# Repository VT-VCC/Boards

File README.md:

# Board Layouts

This repository contains all of the layouts for the custom boards on the CERES cubesat.

- **Motherboard (Rev. C)** - The current main processor board.
- **Communications Board (Rev. A)** - The current combined PINAV GPS and Lithium Radio commications board.
- **GPS Board** and **Radio Board** - These are legacy designs.

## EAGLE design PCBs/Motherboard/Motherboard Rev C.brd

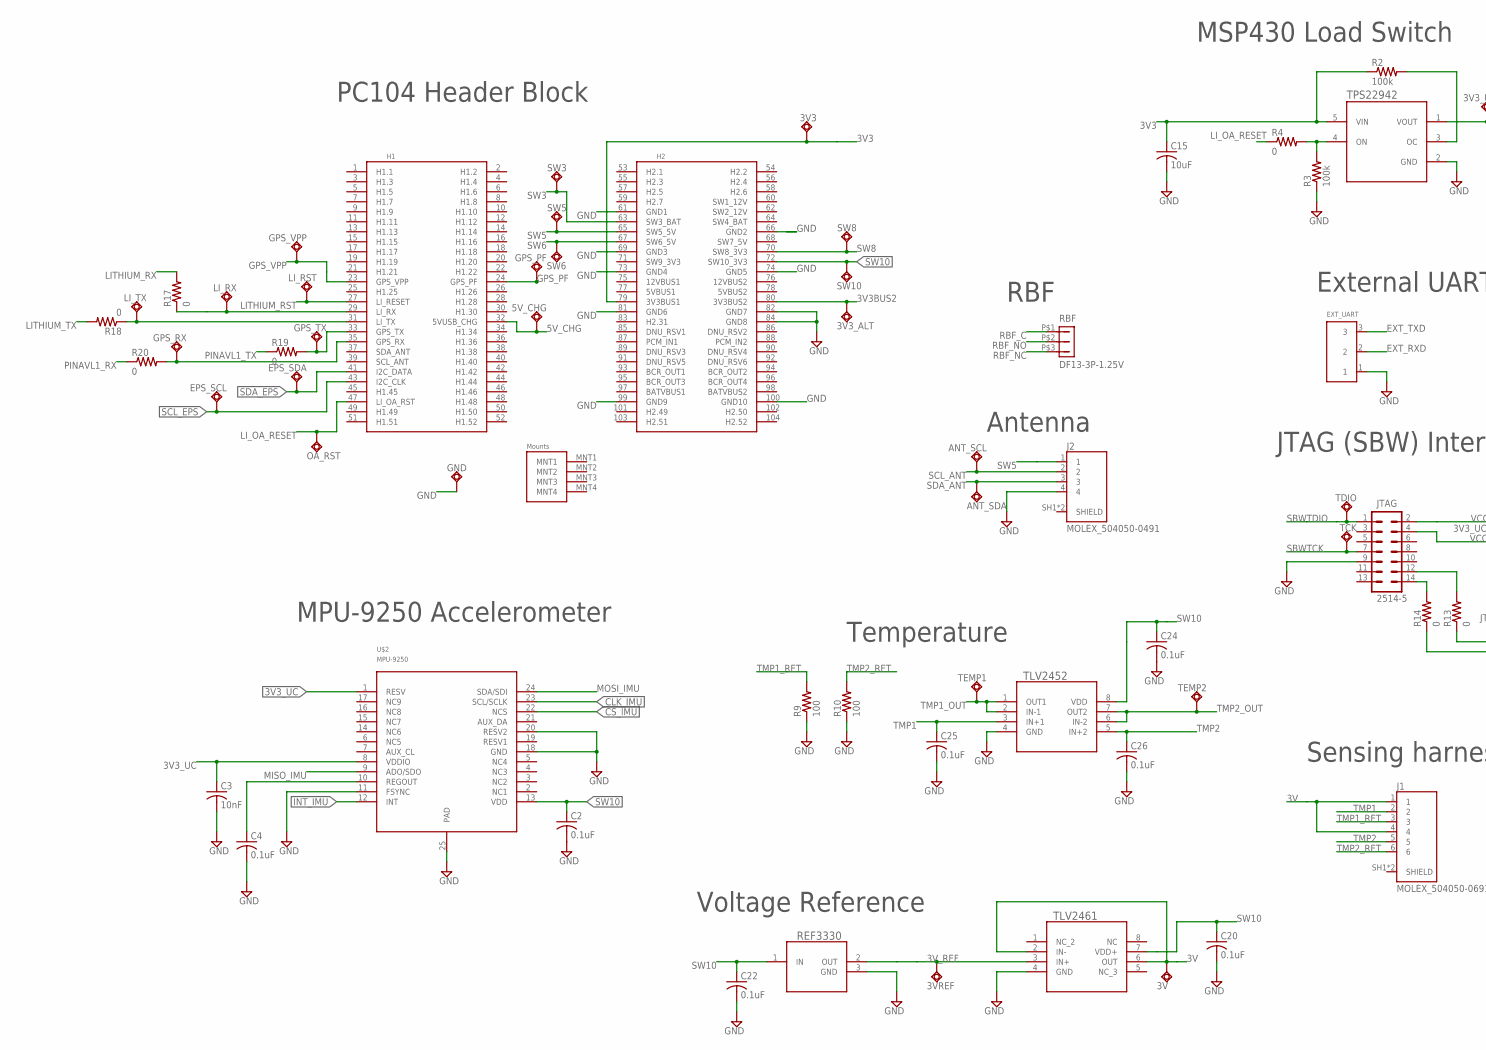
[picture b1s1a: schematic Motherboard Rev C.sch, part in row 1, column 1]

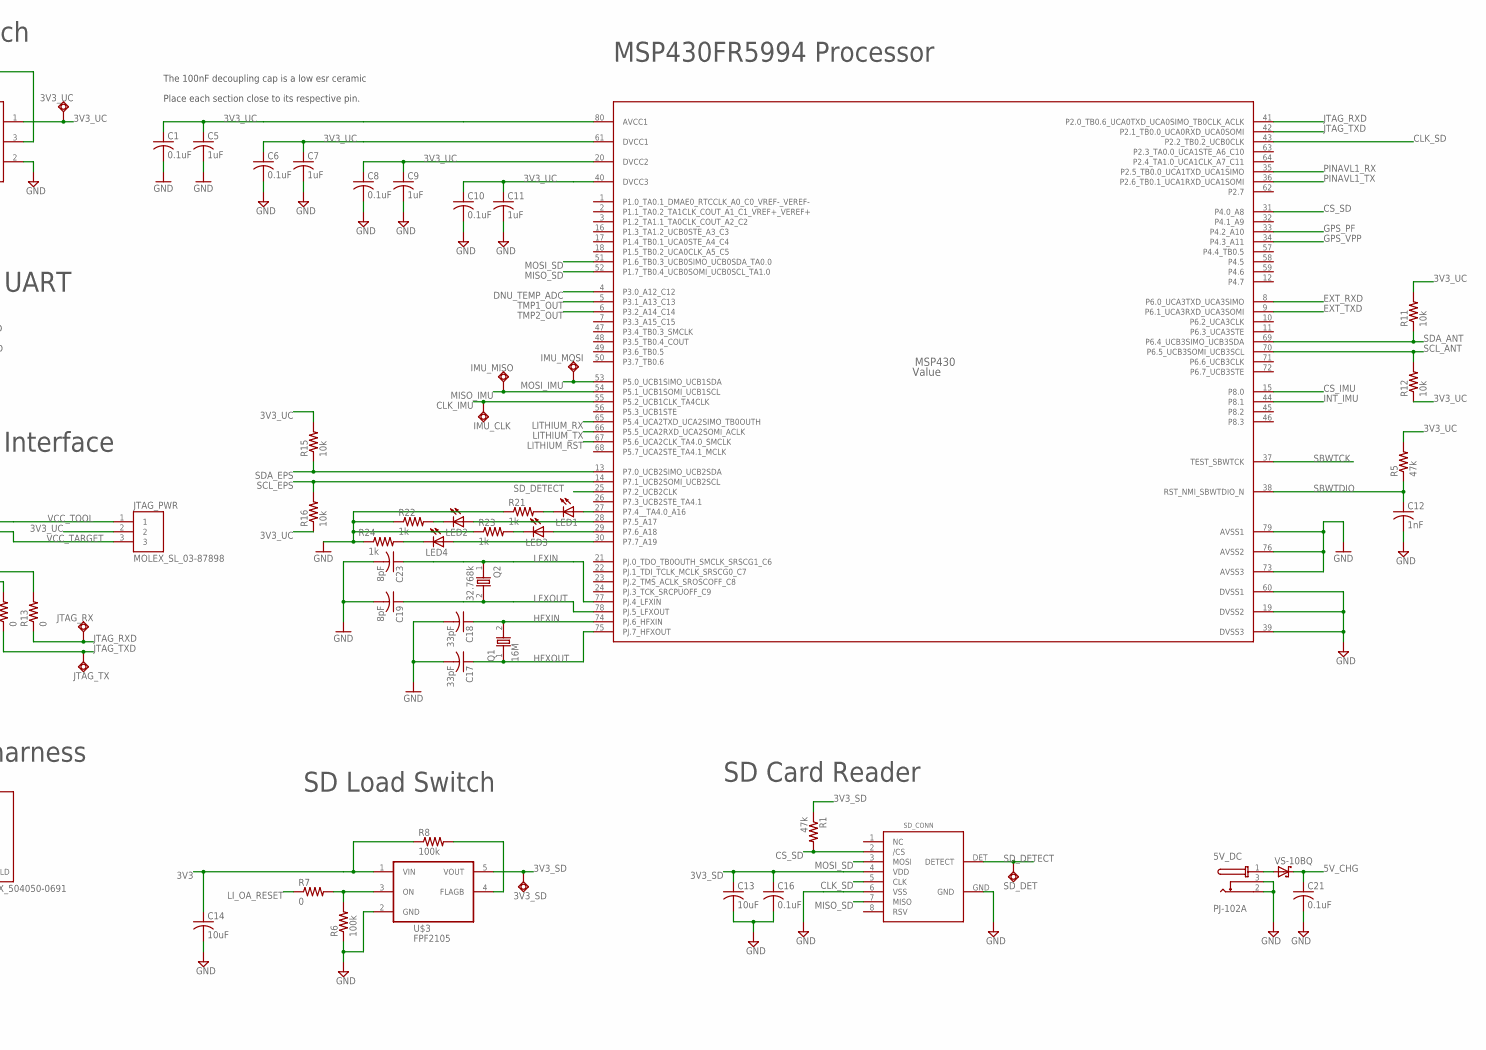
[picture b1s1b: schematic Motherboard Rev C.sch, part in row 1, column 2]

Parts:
3V, 3V3, 3V3_ALT, 3V3_SD, 3V3_UC, 3VREF, 5V_CHG: TPSQTP10SQ; TP10SQ
5V_DC: PJ-102A; CUI_PJ-102A
ANT_SCL: TPSQTP10SQ; TP10SQ
ANT_SDA: TPSQTP10SQ; TP10SQ
C1, C2, C4, C6, C8, C10, C16, C20, C21, C22, C24, C25, C26: 0.1uF; C0805
C3: 10nF; C0805
C5, C7, C9, C11: 1uF; C0805
C12: 1nF; C0805
C13, C14, C15: 10uF; C0805
C17, C18: 33pF; C0805
C19, C23: 8pF; C0805
EPS_SCL: TPSQTP10SQ; TP10SQ
EPS_SDA: TPSQTP10SQ; TP10SQ
EXT_UART: 90121-0763
GND: TPSQTP10SQ; TP10SQ
GPS_PF: TPSQTP10SQ; TP10SQ
GPS_RX: TPSQTP10SQ; TP10SQ
GPS_TX: TPSQTP10SQ; TP10SQ
GPS_VPP: TPSQTP10SQ; TP10SQ
IMU_CLK: TPSQTP06SQ; TP06SQ
IMU_MISO: TPSQTP06SQ; TP06SQ
IMU_MOSI: TPSQTP06SQ; TP06SQ
J1: MOLEX_504050-0691; MOLEX_5040500691
J2: MOLEX_504050-0491; MOLEX_5040500491
JTAG: 2514-5; PAK100/2500-5-14
JTAG_PWR: MOLEX_SL_03-87898; SL_87898_3
JTAG_RX: TPSQTP10SQ; TP10SQ
JTAG_TX: TPSQTP10SQ; TP10SQ
LED1, LED2, LED3, LED4: LEDSML0805; SML0805
LI_RST: TPSQTP10SQ; TP10SQ
LI_RX: TPSQTP10SQ; TP10SQ
LI_TX: TPSQTP10SQ; TP10SQ
MSP430: Value; PN0080A_N
OA_RST: TPSQTP10SQ; TP10SQ
Q1: 16M; 5X3.2
Q2: 32.768k; MS1V-T1K
R1, R5: 47k; R0805
R2, R3, R6, R8: 100k; R0805
R4, R7, R13, R14, R17, R18, R19, R20: 0; R0805
R9, R10: 100; R0805
R11, R12, R15, R16: 10k; R0805
R21, R22, R23, R24: 1k; R0805
RBF: DF13-3P-1.25V; DF13C-3P-1.25V
REF3330: REF3330_DBZ_3; DBZ3
SD_CONN: 502702-0891; 502702
SD_DET: TPSQTP10SQ; TP10SQ
SW3, SW5, SW6, SW8, SW10: TPSQTP10SQ; TP10SQ
TCK: TPSQTP10SQ; TP10SQ
TDIO: TPSQTP10SQ; TP10SQ
TEMP1, TEMP2: TPSQTP10SQ; TP10SQ
TLV2452: TLV2452; D8
TLV2461: TLV2461A_D_8; D8
TPS22942: TPS22942DCKR; DCK0005A
U$1: PC104_NO_DIMENSION
U$2: MPU-9250; LEAD-QFN24
U$3: FPF2105; SOT23-5
VS-10BQ: 10BQ015HM3; SMB

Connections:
3V: 3V.TP, J1.1, J1.4, TLV2461.2 (IN-), TLV2461.6 (OUT)
3V3: 3V3.TP, C14.1, C15.1, R2.1, R8.1, TPS22942.5 (VIN), U$1.79 (3V3BUS1), U$3.1 (VIN)
3V3BUS2: 3V3_ALT.TP, U$1.80 (3V3BUS2)
3V3_SD: 3V3_SD.TP, C13.1, C16.1, R1.1, SD_CONN.4 (VDD), U$3.5 (VOUT)
3V3_UC: 3V3_UC.TP, C1.1, C3.1, C5.1, C6.1, C7.1, C8.1, C9.1, C10.1, C11.1, JTAG_PWR.2, MSP430.20 (DVCC2), MSP430.40 (DVCC3), MSP430.61 (DVCC1), MSP430.80 (AVCC1), R5.2, R11.2, R12.1, R15.2, R16.1, TPS22942.1 (VOUT), U$2.1 (RESV), U$2.8 (VDDIO)
3V_REF: 3VREF.TP, REF3330.2 (OUT), TLV2461.3 (IN+)
5V_CHG: 5V_CHG.TP, C21.1, U$1.32 (5VUSB_CHG), VS-10BQ.C
CLK_IMU: IMU_CLK.TP, MSP430.55 (P5.2_UCB1CLK_TA4CLK), U$2.23 (SCL/SCLK)
CLK_SD: MSP430.43 (P2.2_TB0.2_UCB0CLK), SD_CONN.5 (CLK)
CS_IMU: MSP430.15 (P8.0), U$2.22 (NCS)
CS_SD: MSP430.31 (P4.0_A8), R1.2, SD_CONN.2 (/CS)
DNU_TEMP_ADC: MSP430.4 (P3.0_A12_C12)
EXT_RXD: EXT_UART.2, MSP430.8 (P6.0_UCA3TXD_UCA3SIMO)
EXT_TXD: EXT_UART.3, MSP430.9 (P6.1_UCA3RXD_UCA3SOMI)
GND: 5V_DC.2, 5V_DC.3, C1.2, C2.2, C3.2, C4.2, C5.2, C6.2, C7.2, C8.2, C9.2, C10.2, C11.2, C12.2, C13.2, C14.2, C15.2, C16.2, C17.2, C18.2, C19.2, C20.2, C21.2, C22.2, C23.2, C24.2, C25.2, C26.2, EXT_UART.1, GND.TP, J2.4, JTAG.9, MSP430.19 (DVSS2), MSP430.39 (DVSS3), MSP430.60 (DVSS1), MSP430.73 (AVSS3), MSP430.76 (AVSS2), MSP430.79 (AVSS1), R3.1, R6.1, R9.1, R10.1, R21.1, R22.1, R23.1, R24.1, REF3330.3 (GND), SD_CONN.6 (VSS), SD_CONN.GND, TLV2452.4 (GND), TLV2461.4 (GND), TPS22942.2 (GND), U$1.61 (GND1), U$1.66 (GND2), U$1.69 (GND3), U$1.73 (GND4), U$1.74 (GND5), U$1.81 (GND6), U$1.82 (GND7), U$1.84 (GND8), U$1.99 (GND9), U$1.100 (GND10), U$2.11 (FSYNC), U$2.18 (GND), U$2.20 (RESV2), U$2.25 (PAD), U$3.2 (GND)
GPS_PF: GPS_PF.TP, MSP430.33 (P4.2_A10), U$1.24 (GPS_PF)
GPS_VPP: GPS_VPP.TP, MSP430.34 (P4.3_A11), U$1.23 (GPS_VPP)
HFXIN: C18.1, MSP430.74 (PJ.6_HFXIN), Q1.2
HFXOUT: C17.1, MSP430.75 (PJ.7_HFXOUT), Q1.1
INT_IMU: MSP430.44 (P8.1), U$2.12 (INT)
JTAG_RXD: JTAG_RX.TP, MSP430.41 (P2.0_TB0.6_UCA0TXD_UCA0SIMO_TB0CLK_ACLK), R13.1
JTAG_TXD: JTAG_TX.TP, MSP430.42 (P2.1_TB0.0_UCA0RXD_UCA0SOMI), R14.1
LFXIN: C23.1, MSP430.77 (PJ.4_LFXIN), Q2.1
LFXOUT: C19.1, MSP430.78 (PJ.5_LFXOUT), Q2.2
LITHIUM_RST: LI_RST.TP, MSP430.67 (P5.6_UCA2CLK_TA4.0_SMCLK), U$1.27 (LI_RESET)
LITHIUM_RX: MSP430.65 (P5.4_UCA2TXD_UCA2SIMO_TB0OUTH), R17.2
LITHIUM_TX: MSP430.66 (P5.5_UCA2RXD_UCA2SOMI_ACLK), R18.2
LI_OA_RESET: OA_RST.TP, R4.1, R7.1, U$1.47 (LI_OA_RST)
MISO_IMU: IMU_MISO.TP, MSP430.54 (P5.1_UCB1SOMI_UCB1SCL), U$2.9 (ADO/SDO)
MISO_SD: MSP430.52 (P1.7_TB0.4_UCB0SOMI_UCB0SCL_TA1.0), SD_CONN.7 (MISO)
MOSI_IMU: IMU_MOSI.TP, MSP430.53 (P5.0_UCB1SIMO_UCB1SDA), U$2.24 (SDA/SDI)
MOSI_SD: MSP430.51 (P1.6_TB0.3_UCB0SIMO_UCB0SDA_TA0.0), SD_CONN.3 (MOSI)
unnamed: R2.2, TPS22942.3 (OC)
unnamed: R6.2, R7.2, U$3.3 (ON)
unnamed: C4.1, U$2.10 (REGOUT)
unnamed: LED1.C, R21.2
unnamed: R3.2, R4.2, TPS22942.4 (ON)
unnamed: LED1.A, MSP430.27 (P7.4__TA4.0_A16)
unnamed: R8.2, U$3.4 (FLAGB)
unnamed: JTAG.14, R14.2
unnamed: LED2.A, MSP430.28 (P7.5_A17)
unnamed: LED2.C, R22.2
unnamed: JTAG.12, R13.2
unnamed: LED3.A, MSP430.29 (P7.6_A18)
unnamed: 5V_DC.1, VS-10BQ.A
unnamed: LED3.C, R23.2
unnamed: LED4.A, MSP430.30 (P7.7_A19)
unnamed: LED4.C, R24.2
unnamed: GPS_RX.TP, R20.2, U$1.35 (GPS_RX)
unnamed: GPS_TX.TP, R19.2, U$1.33 (GPS_TX)
unnamed: LI_TX.TP, R18.1, U$1.31 (LI_TX)
unnamed: LI_RX.TP, R17.1, U$1.29 (LI_RX)
PINAVL1_RX: MSP430.35 (P2.5_TB0.0_UCA1TXD_UCA1SIMO), R20.1
PINAVL1_TX: MSP430.36 (P2.6_TB0.1_UCA1RXD_UCA1SOMI), R19.1
RBF_C: RBF.P$1 (1)
RBF_NC: RBF.P$3 (3)
RBF_NO: RBF.P$2 (2)
SBWTCK: JTAG.7, MSP430.37 (TEST_SBWTCK), TCK.TP
SBWTDIO: C12.1, JTAG.1, MSP430.38 (RST_NMI_SBWTDIO_N), R5.1, TDIO.TP
SCL_ANT: ANT_SCL.TP, J2.2, MSP430.70 (P6.5_UCB3SOMI_UCB3SCL), R12.2
SCL_EPS: EPS_SCL.TP, MSP430.14 (P7.1_UCB2SOMI_UCB2SCL), R16.2, U$1.43 (I2C_CLK)
SDA_ANT: ANT_SDA.TP, J2.3, MSP430.69 (P6.4_UCB3SIMO_UCB3SDA), R11.1
SDA_EPS: EPS_SDA.TP, MSP430.13 (P7.0_UCB2SIMO_UCB2SDA), R15.1, U$1.41 (I2C_DATA)
SD_DETECT: MSP430.25 (P7.2_UCB2CLK), SD_CONN.DET (DETECT), SD_DET.TP
SHIELD: J1.SH1 (SHIELD), J1.SH2 (SHIELD), J2.SH1 (SHIELD), J2.SH2 (SHIELD)
SW3: SW3.TP, U$1.63 (SW3_BAT)
SW5: J2.1, SW5.TP, U$1.65 (SW5_5V)
SW6: SW6.TP, U$1.67 (SW6_5V)
SW8: SW8.TP, U$1.70 (SW8_3V3)
SW10: C2.1, C20.1, C22.1, C24.1, REF3330.1 (IN), SW10.TP, TLV2452.8 (VDD), TLV2461.7 (VDD+), U$1.72 (SW10_3V3), U$2.13 (VDD)
TMP1: C25.1, J1.2, TLV2452.3 (IN+1)
TMP1_OUT: MSP430.5 (P3.1_A13_C13), TEMP1.TP, TLV2452.1 (OUT1), TLV2452.2 (IN-1)
TMP1_RET: J1.3, R9.2
TMP2: C26.1, J1.5, TLV2452.5 (IN+2)
TMP2_OUT: MSP430.6 (P3.2_A14_C14), TEMP2.TP, TLV2452.6 (IN-2), TLV2452.7 (OUT2)
TMP2_RET: J1.6, R10.2
VCC_TARGET: JTAG.4, JTAG_PWR.3
VCC_TOOL: JTAG.2, JTAG_PWR.1

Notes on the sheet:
MPU-9250 Accelerometer
MSP430FR5994 Processor
PC104 Header Block
The 100nF decoupling cap is a low esr ceramic
Place each section close to its respective pin.
SD Card Reader
JTAG (SBW) Interface
Sensing harness
MSP430 Load Switch
SD Load Switch
Temperature
Voltage Reference
Antenna
External UART
RBF

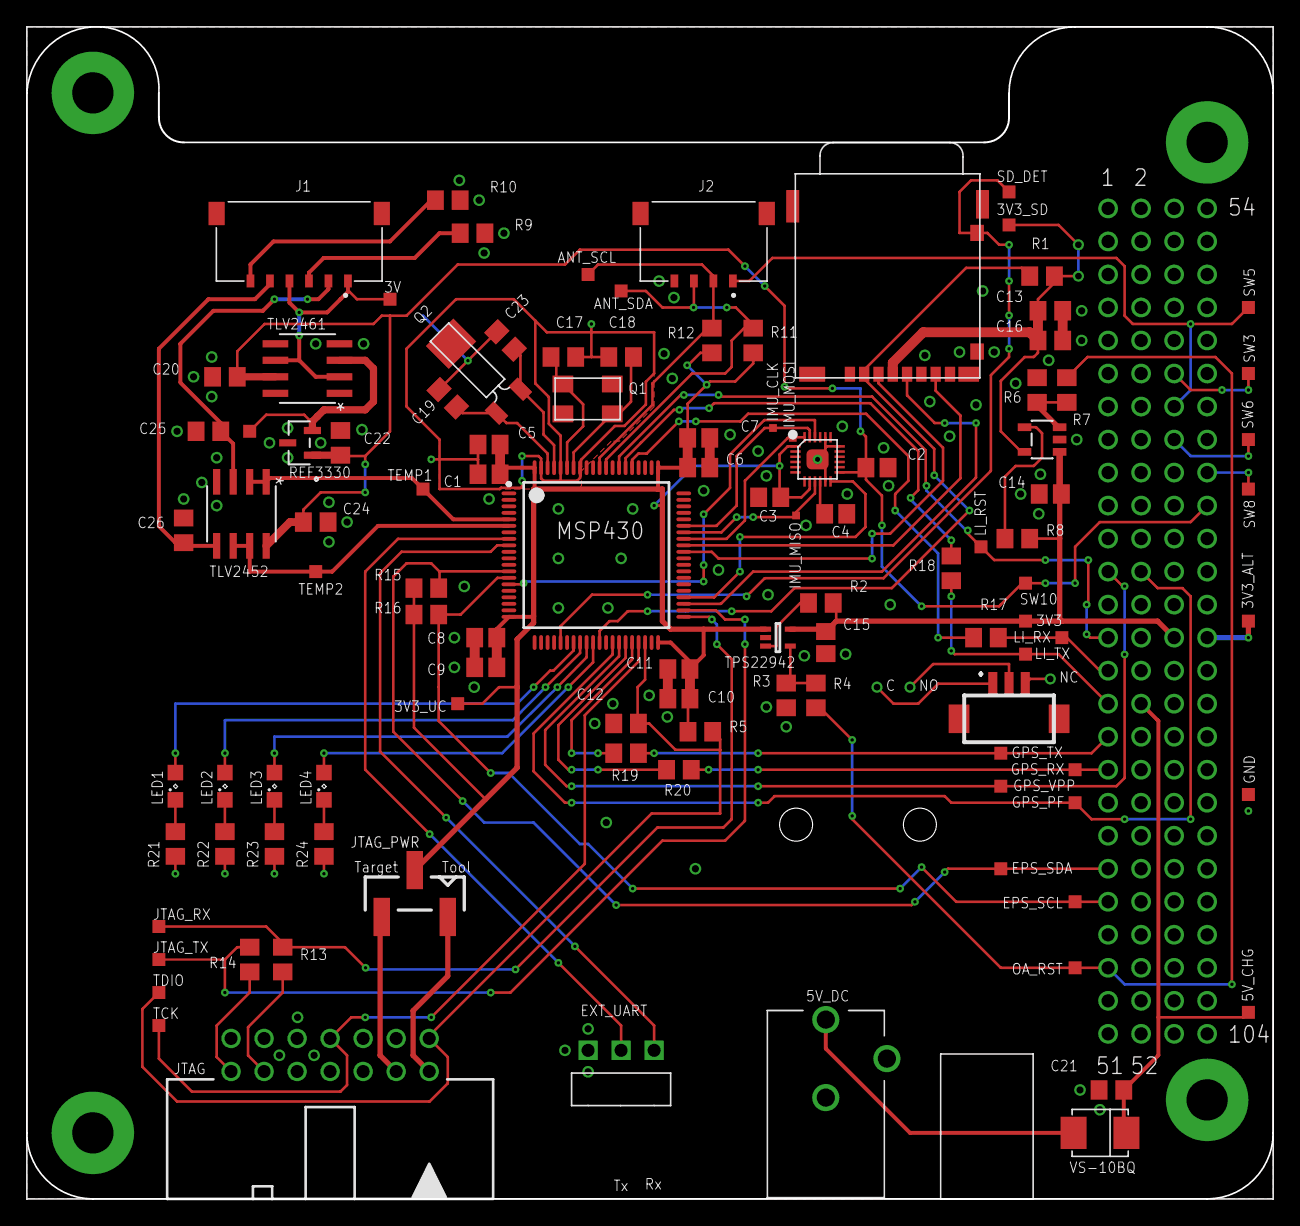
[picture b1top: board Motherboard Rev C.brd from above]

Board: 2 copper layers, 95.9 x 90.2 mm, 109 parts (0 on the bottom side), 74 nets.

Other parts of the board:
U$4: RBF_MOUNT

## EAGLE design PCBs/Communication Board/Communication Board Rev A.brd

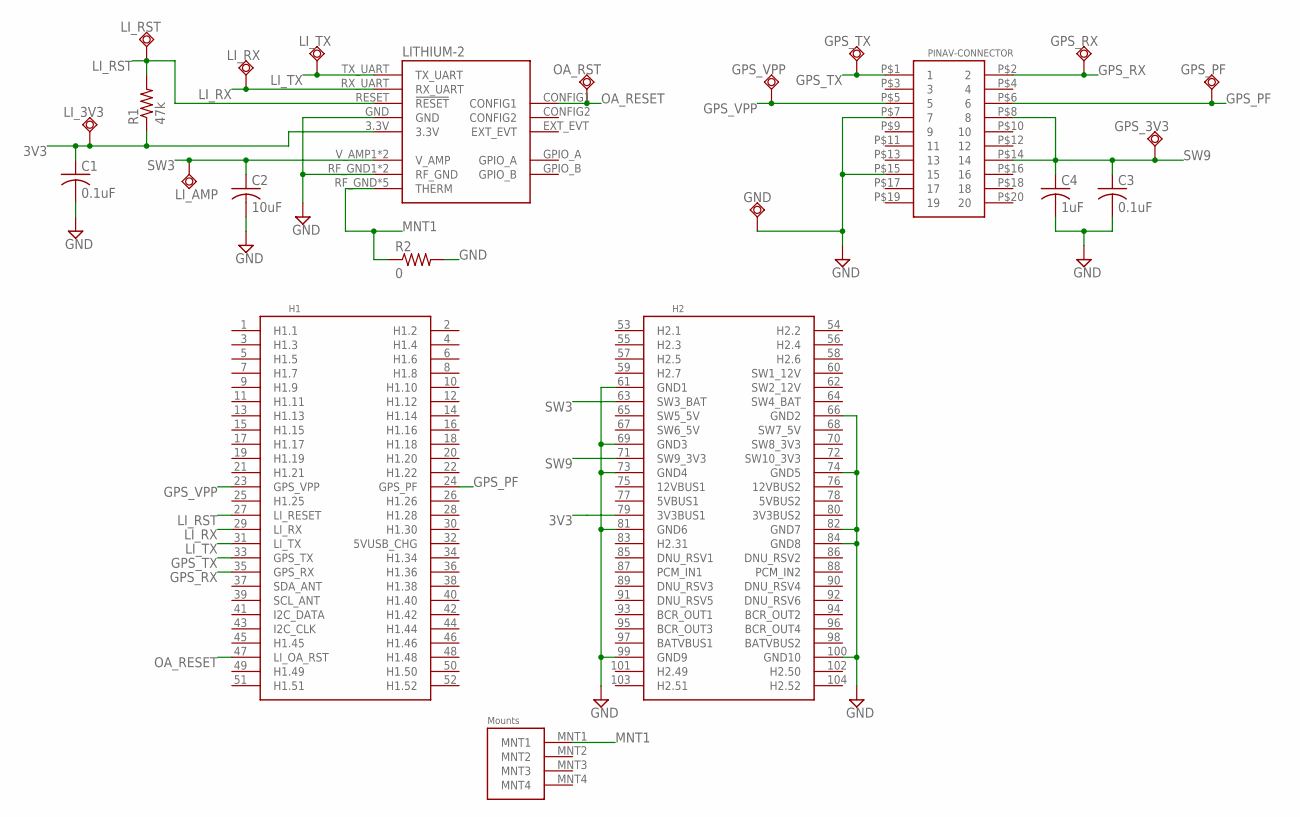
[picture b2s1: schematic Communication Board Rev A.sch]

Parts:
C1, C3: 0.1uF; C0805
C2: 10uF; C0805
C4: 1uF; C0805
GND: TPSQTP10SQ; TP10SQ
GPS_3V3: TPSQTP10SQ; TP10SQ
GPS_PF: TPSQTP10SQ; TP10SQ
GPS_RX: TPSQTP10SQ; TP10SQ
GPS_TX: TPSQTP10SQ; TP10SQ
GPS_VPP: TPSQTP10SQ; TP10SQ
LITHIUM-2: LI-2
LI_3V3: TPSQTP10SQ; TP10SQ
LI_AMP: TPSQTP10SQ; TP10SQ
LI_RST: TPSQTP10SQ; TP10SQ
LI_RX: TPSQTP10SQ; TP10SQ
LI_TX: TPSQTP10SQ; TP10SQ
OA_RST: TPSQTP10SQ; TP10SQ
PINAV-CONNECTOR: HLE-110-02-X-DVHLE-110-X-DV-PE-BA; HLE-110-02-X-DV-PE-BE
R1: 47k; R0805
R2: 0; R0805
U$1: PC104_NO_DIMENSION

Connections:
3V3: C1.1, LITHIUM-2.3.3V, LI_3V3.TP, R1.1, U$1.79 (3V3BUS1)
GND: C1.2, C2.2, C3.2, C4.2, GND.TP, LITHIUM-2.GND, LITHIUM-2.RF_GND1 (RF_GND), LITHIUM-2.RF_GND2 (RF_GND), PINAV-CONNECTOR.P$7 (7), PINAV-CONNECTOR.P$15 (15), R2.2, U$1.61 (GND1), U$1.66 (GND2), U$1.69 (GND3), U$1.73 (GND4), U$1.74 (GND5), U$1.81 (GND6), U$1.82 (GND7), U$1.84 (GND8), U$1.99 (GND9), U$1.100 (GND10)
GPS_PF: GPS_PF.TP, PINAV-CONNECTOR.P$6 (6), U$1.24 (GPS_PF)
GPS_RX: GPS_RX.TP, PINAV-CONNECTOR.P$2 (2), U$1.35 (GPS_RX)
GPS_TX: GPS_TX.TP, PINAV-CONNECTOR.P$1 (1), U$1.33 (GPS_TX)
GPS_VPP: GPS_VPP.TP, PINAV-CONNECTOR.P$5 (5), U$1.23 (GPS_VPP)
LI_RST: LITHIUM-2.RESET (!RESET), LI_RST.TP, R1.2, U$1.27 (LI_RESET)
LI_RX: LITHIUM-2.RX_UART, LI_RX.TP, U$1.29 (LI_RX)
LI_TX: LITHIUM-2.TX_UART, LI_TX.TP, U$1.31 (LI_TX)
MNT1: LITHIUM-2.RF_GND (THERM), LITHIUM-2.THERM1 (THERM), LITHIUM-2.THERM2 (THERM), LITHIUM-2.THERM3 (THERM), LITHIUM-2.THERM4 (THERM), R2.1, U$1.MNT1
OA_RESET: LITHIUM-2.CONFIG1, OA_RST.TP, U$1.47 (LI_OA_RST)
SW3: C2.1, LITHIUM-2.V_AMP1 (V_AMP), LITHIUM-2.V_AMP2 (V_AMP), LI_AMP.TP, U$1.63 (SW3_BAT)
SW9: C3.1, C4.1, GPS_3V3.TP, PINAV-CONNECTOR.P$8 (8), PINAV-CONNECTOR.P$14 (14), U$1.71 (SW9_3V3)

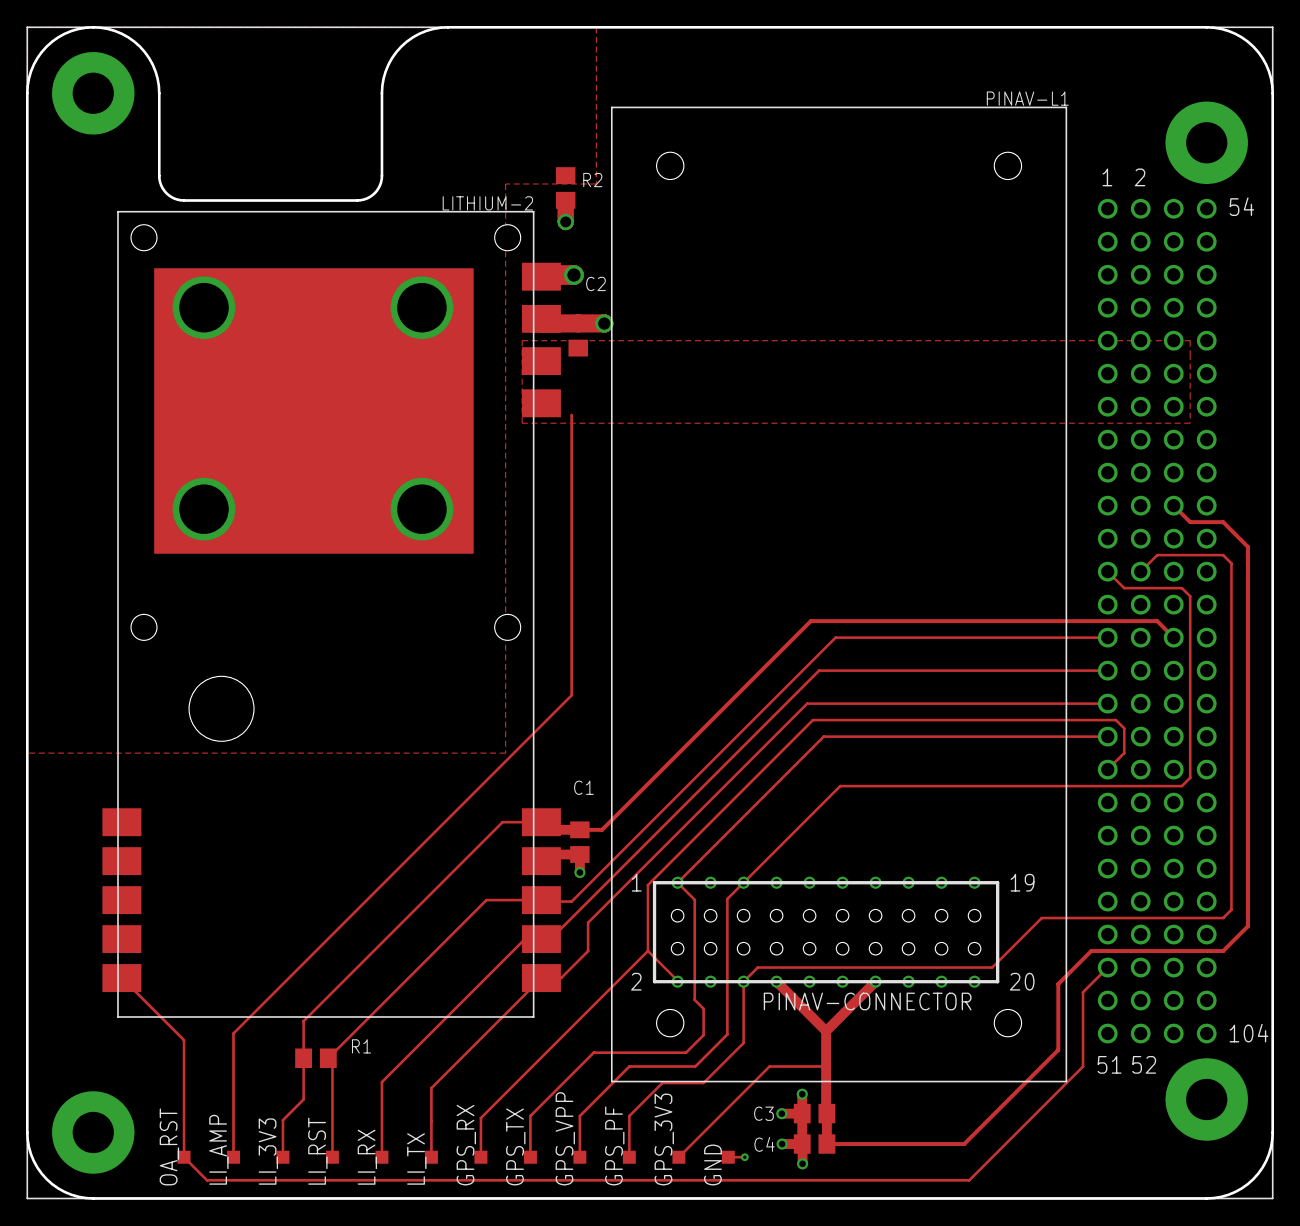
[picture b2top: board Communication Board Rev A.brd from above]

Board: 2 copper layers, 95.9 x 90.2 mm, 22 parts (0 on the bottom side), 13 nets.

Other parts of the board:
PINAV-L1: PINAV-L1

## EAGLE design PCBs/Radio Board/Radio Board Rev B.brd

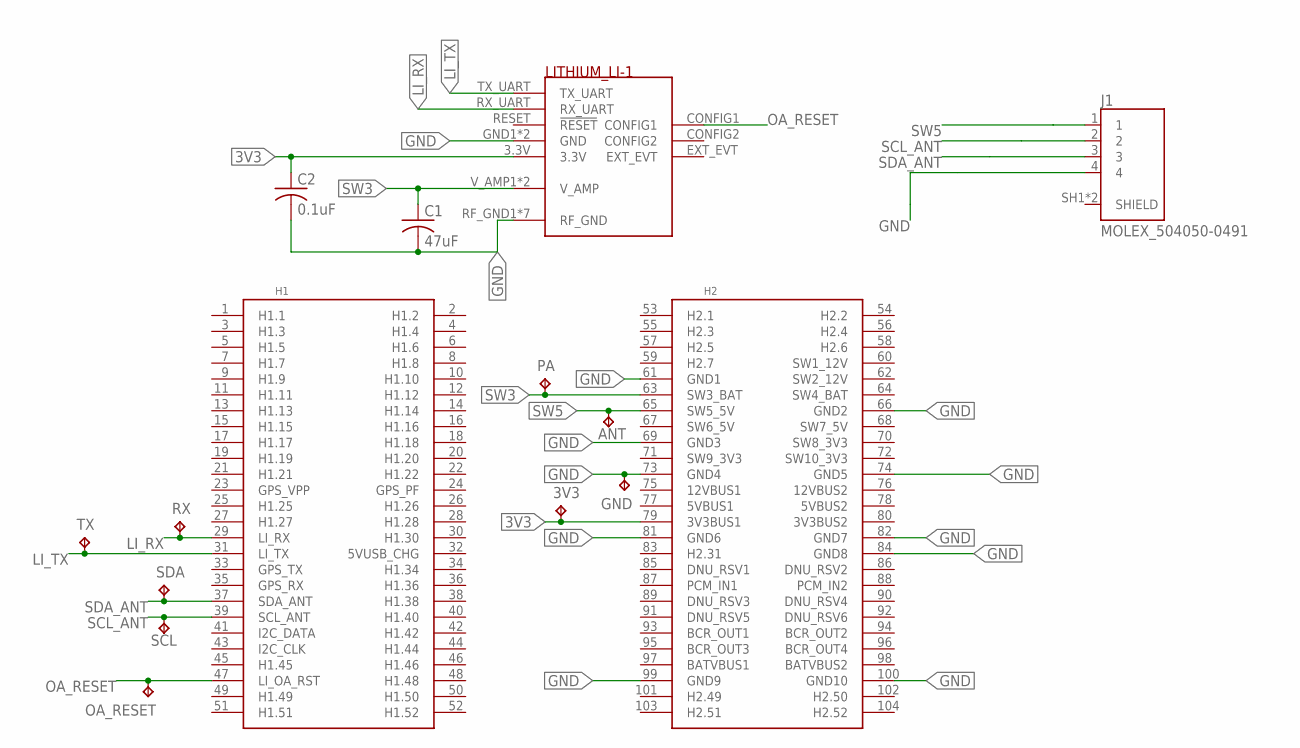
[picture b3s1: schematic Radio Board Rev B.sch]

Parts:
3V3: TPTP10SQ; TP10SQ
ANT: TPTP10SQ; TP10SQ
C1: 47uF; C0805
C2: 0.1uF; C0805
GND: TPTP10SQ; TP10SQ
J1: MOLEX_504050-0491; MOLEX_5040500491
LI-1: LI-1
OA_RESET: TPTP10SQ; TP10SQ
PA: TPTP10SQ; TP10SQ
RX: TPTP10SQ; TP10SQ
SCL: TPTP10SQ; TP10SQ
SDA: TPTP10SQ; TP10SQ
TX: TPTP10SQ; TP10SQ
U$1: PC104_NO_DIMENSION

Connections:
3V3: 3V3.TP, C2.1, LI-1.3.3V, U$1.79 (3V3BUS1)
GND: C1.2, C2.2, GND.TP, J1.4, LI-1.GND1 (GND), LI-1.GND2 (GND), LI-1.RF_GND1 (RF_GND), LI-1.RF_GND2 (RF_GND), LI-1.RF_GND3 (RF_GND), LI-1.THERM1 (RF_GND), LI-1.THERM2 (RF_GND), LI-1.THERM3 (RF_GND), LI-1.THERM4 (RF_GND), U$1.61 (GND1), U$1.66 (GND2), U$1.69 (GND3), U$1.73 (GND4), U$1.74 (GND5), U$1.81 (GND6), U$1.82 (GND7), U$1.84 (GND8), U$1.99 (GND9), U$1.100 (GND10)
LI_RX: LI-1.RX_UART, RX.TP, U$1.29 (LI_RX)
LI_TX: LI-1.TX_UART, TX.TP, U$1.31 (LI_TX)
OA_RESET: LI-1.CONFIG1, OA_RESET.TP, U$1.47 (LI_OA_RST)
SCL_ANT: J1.2, SCL.TP, U$1.39 (SCL_ANT)
SDA_ANT: J1.3, SDA.TP, U$1.37 (SDA_ANT)
SHIELD: J1.SH1 (SHIELD), J1.SH2 (SHIELD)
SW3: C1.1, LI-1.V_AMP1 (V_AMP), LI-1.V_AMP2 (V_AMP), PA.TP, U$1.63 (SW3_BAT)
SW5: ANT.TP, J1.1, U$1.65 (SW5_5V)

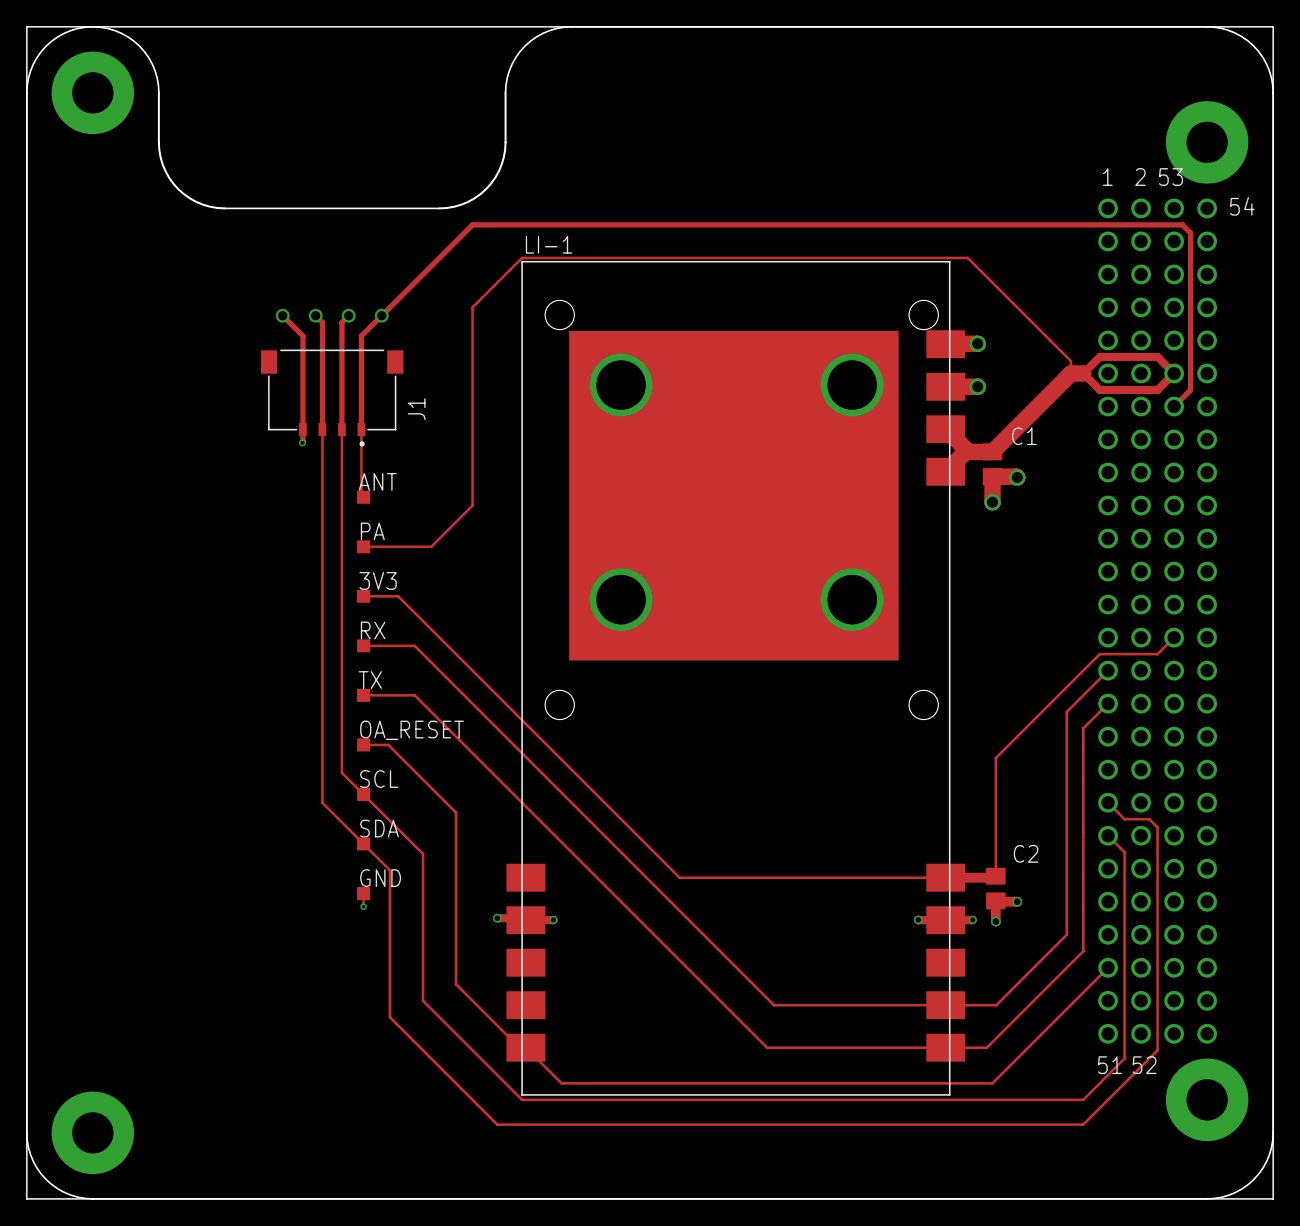
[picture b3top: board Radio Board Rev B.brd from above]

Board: 2 copper layers, 95.9 x 90.2 mm, 14 parts (0 on the bottom side), 10 nets.

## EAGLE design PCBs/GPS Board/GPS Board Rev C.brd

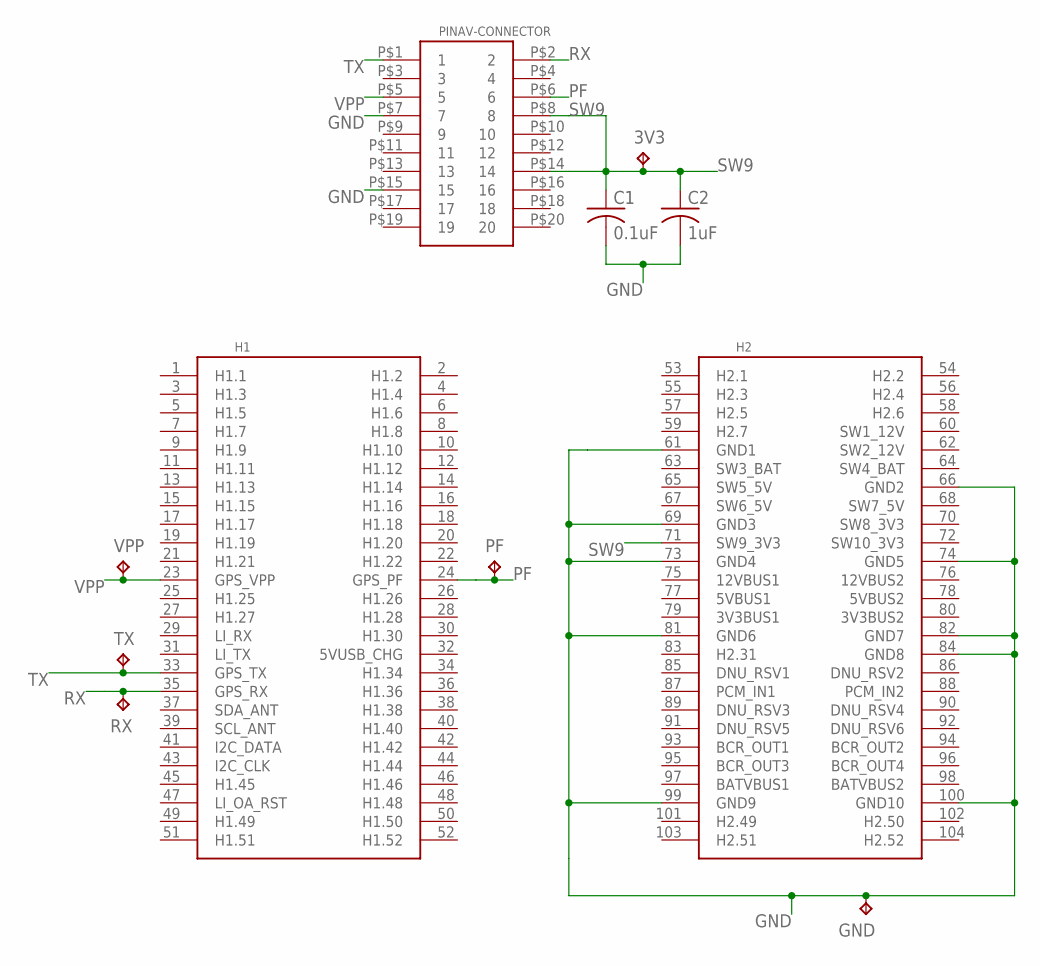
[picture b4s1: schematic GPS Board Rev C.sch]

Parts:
3V3: TPTP10SQ; TP10SQ
C1: 0.1uF; C0805
C2: 1uF; C0805
GND: TPTP10SQ; TP10SQ
PF: TPTP10SQ; TP10SQ
PINAV-CONNECTOR: HLE-110-02-X-DVHLE-110-X-DV-PE-BA; HLE-110-02-X-DV-PE-BE
RX: TPTP10SQ; TP10SQ
TX: TPTP10SQ; TP10SQ
U$2: PC104_NO_DIMENSION
VPP: TPTP10SQ; TP10SQ

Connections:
GND: C1.2, C2.2, GND.TP, PINAV-CONNECTOR.P$7 (7), PINAV-CONNECTOR.P$15 (15), U$2.61 (GND1), U$2.66 (GND2), U$2.69 (GND3), U$2.73 (GND4), U$2.74 (GND5), U$2.81 (GND6), U$2.82 (GND7), U$2.84 (GND8), U$2.99 (GND9), U$2.100 (GND10)
PF: PF.TP, PINAV-CONNECTOR.P$6 (6), U$2.24 (GPS_PF)
RX: PINAV-CONNECTOR.P$2 (2), RX.TP, U$2.35 (GPS_RX)
SW9: 3V3.TP, C1.1, C2.1, PINAV-CONNECTOR.P$8 (8), PINAV-CONNECTOR.P$14 (14), U$2.71 (SW9_3V3)
TX: PINAV-CONNECTOR.P$1 (1), TX.TP, U$2.33 (GPS_TX)
VPP: PINAV-CONNECTOR.P$5 (5), U$2.23 (GPS_VPP), VPP.TP

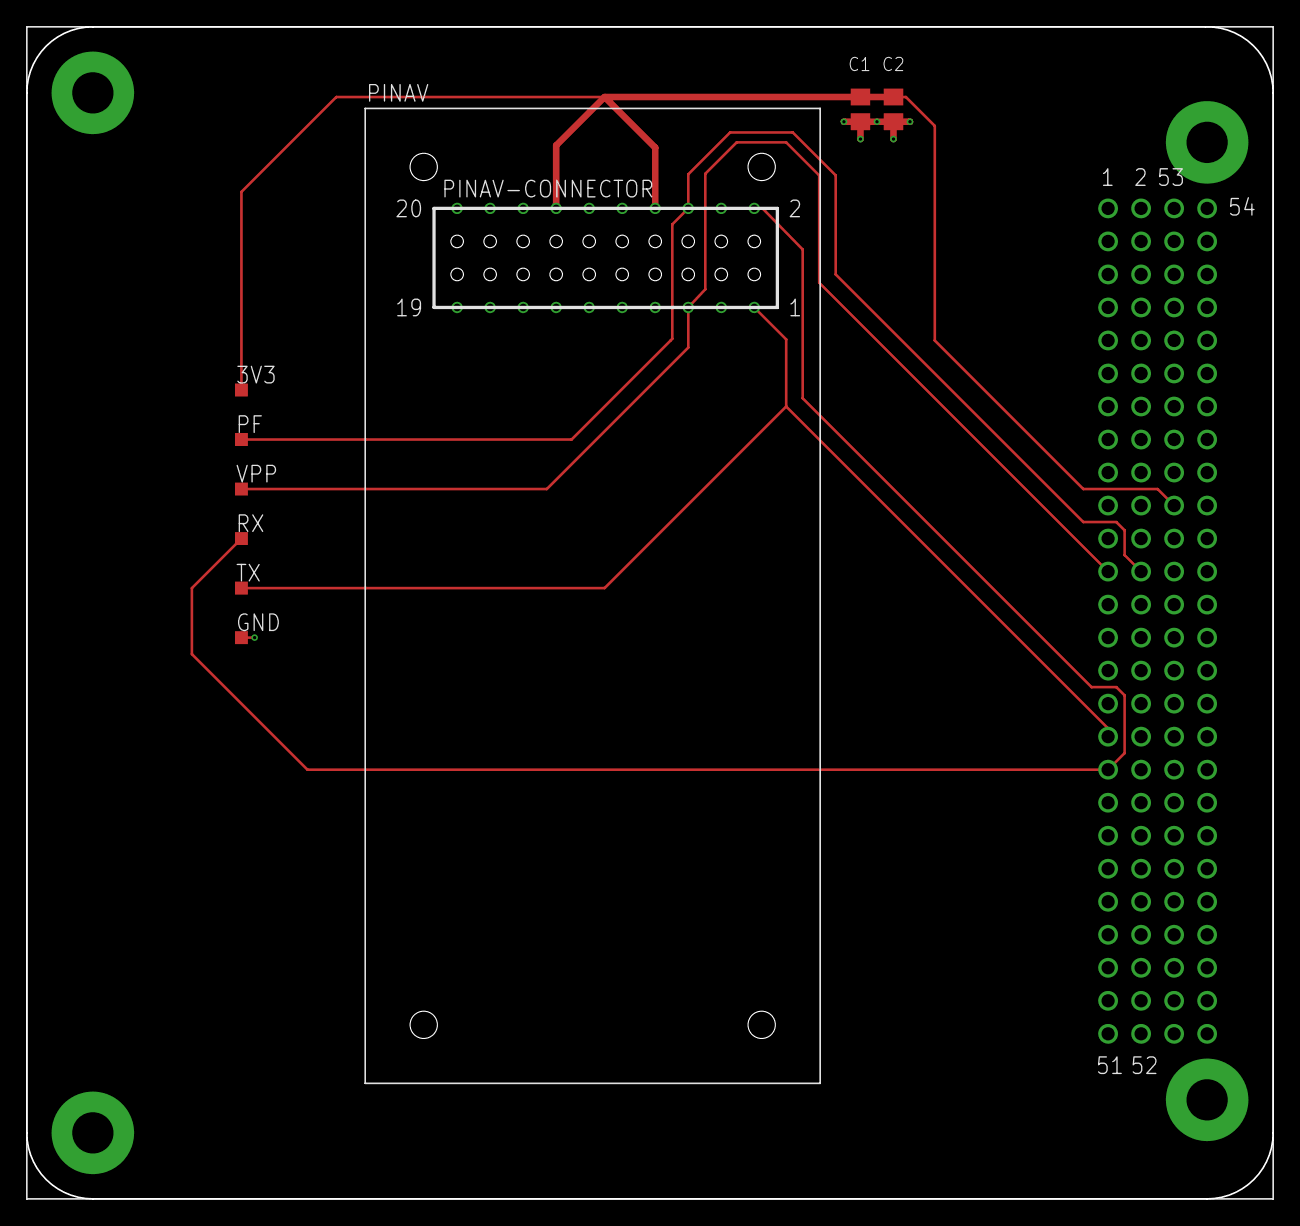
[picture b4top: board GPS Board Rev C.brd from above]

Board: 2 copper layers, 95.9 x 90.2 mm, 11 parts (0 on the bottom side), 6 nets.

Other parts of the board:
PINAV: PINAV-L1

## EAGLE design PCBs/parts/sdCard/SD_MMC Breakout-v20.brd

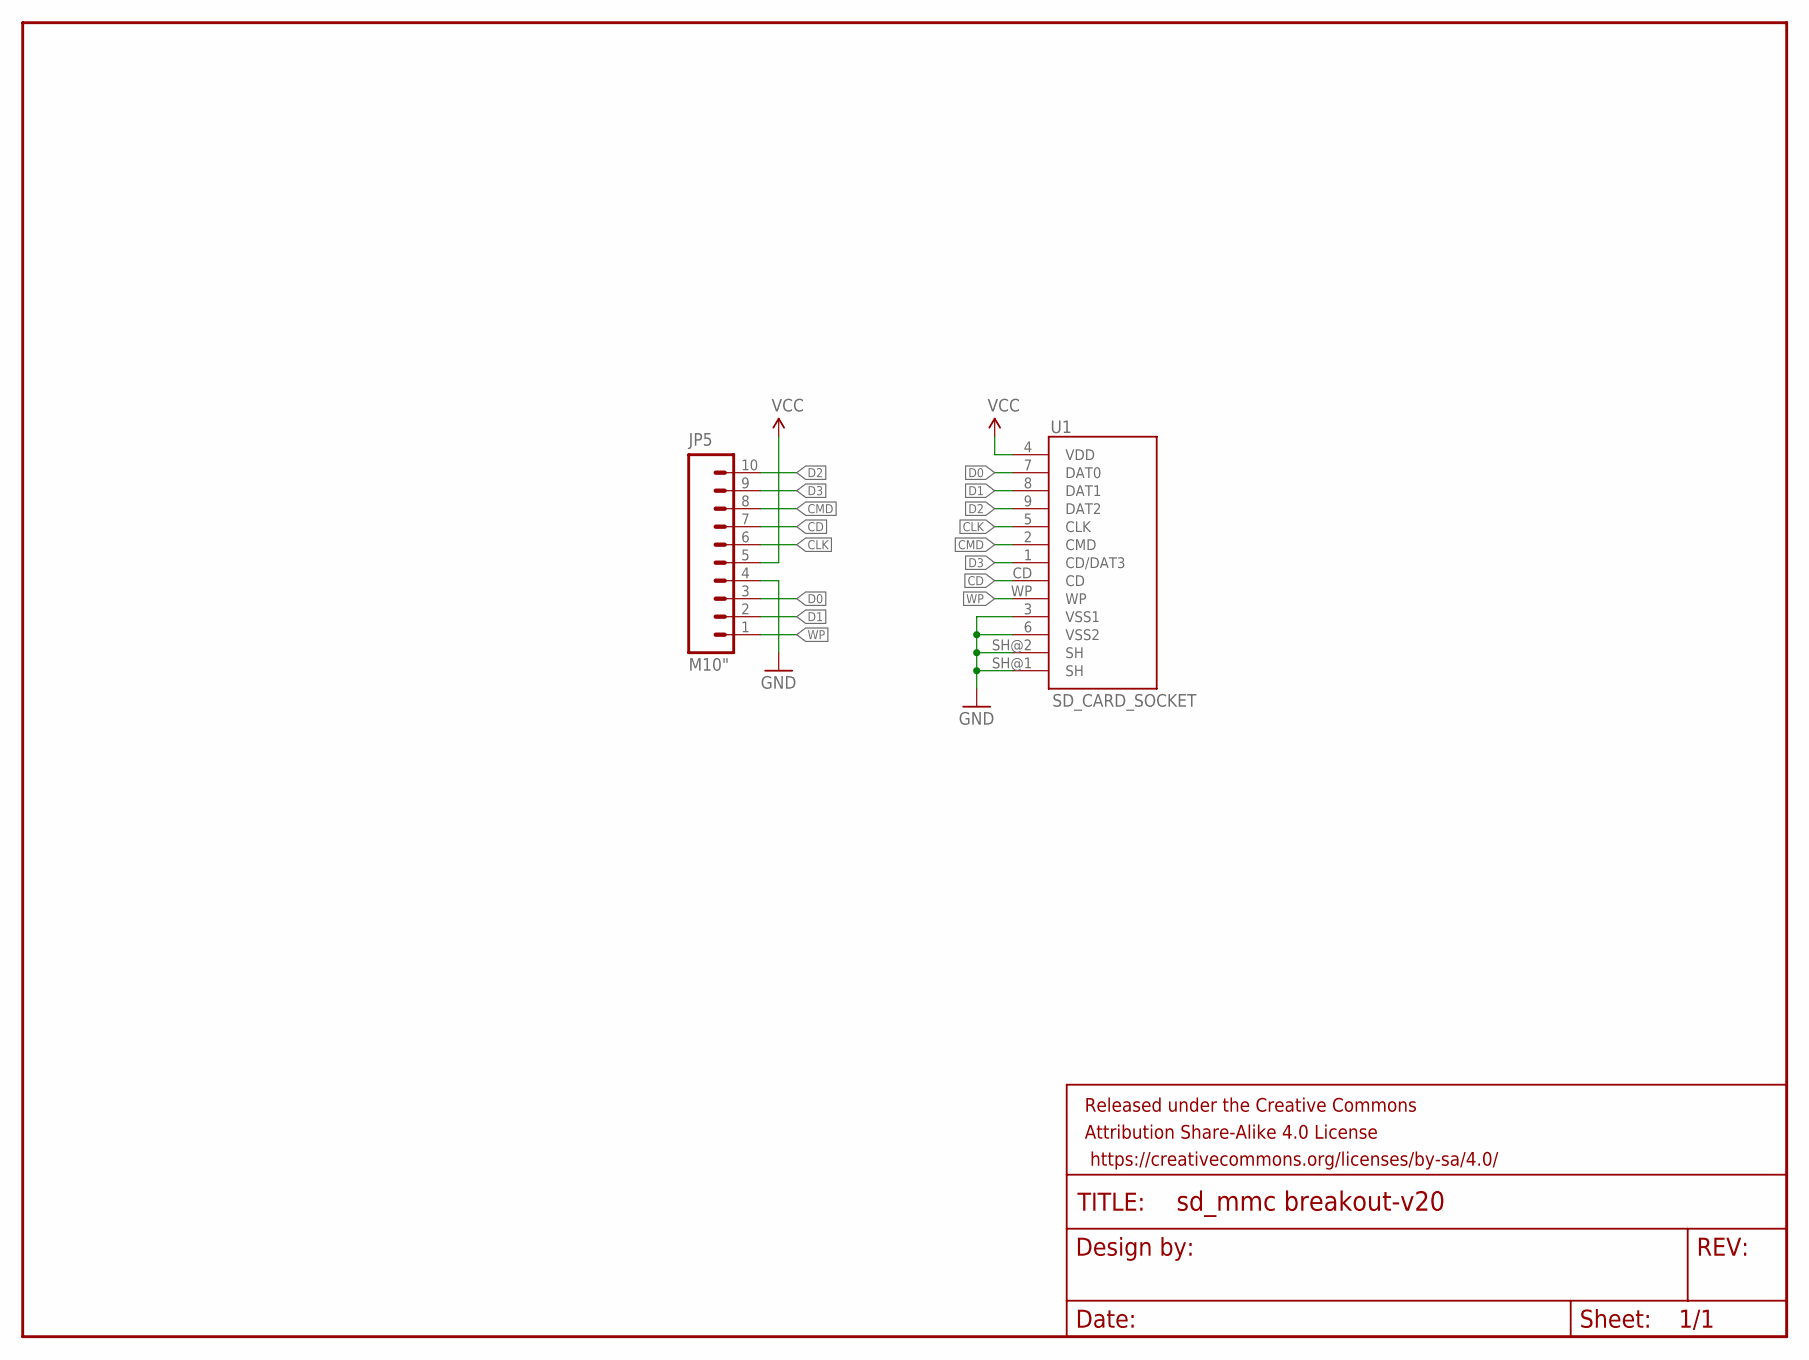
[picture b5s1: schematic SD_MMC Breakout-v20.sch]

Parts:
FRAME1: FRAME-LETTER; CREATIVE_COMMONS
JP5: M10"; 1X10
U1: SD_CARD_SOCKET; SD_1:1

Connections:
CD: JP5.7, U1.CD
CLK: JP5.6, U1.5 (CLK)
CMD: JP5.8, U1.2 (CMD)
D0: JP5.3, U1.7 (DAT0)
D1: JP5.2, U1.8 (DAT1)
D2: JP5.10, U1.9 (DAT2)
D3: JP5.9, U1.1 (CD/DAT3)
GND: JP5.4, U1.3 (VSS1), U1.6 (VSS2), U1.SH@1 (SH), U1.SH@2 (SH)
VCC: JP5.5, U1.4 (VDD)
WP: JP5.1, U1.WP

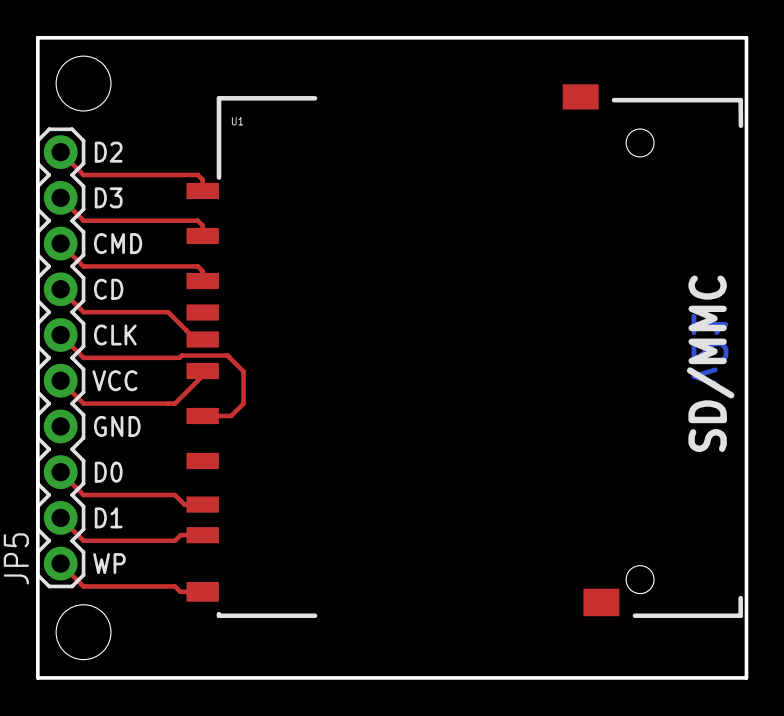
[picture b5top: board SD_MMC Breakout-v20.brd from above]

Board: 2 copper layers, 39.4 x 35.6 mm, 5 parts (0 on the bottom side), 10 nets.

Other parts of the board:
U$4, U$5: STAND-OFF-TIGHT

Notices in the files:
parts and their libraries:
SparkFun-Connectors: Licensing: CC v3.0 Share-Alike You are welcome to use this library for commercial purposes.
SparkFun-Aesthetics: Released under the Creative Commons Attribution Share-Alike 4.0 License
SparkFun-Aesthetics: https://creativecommons.org/licenses/by-sa/4.0
